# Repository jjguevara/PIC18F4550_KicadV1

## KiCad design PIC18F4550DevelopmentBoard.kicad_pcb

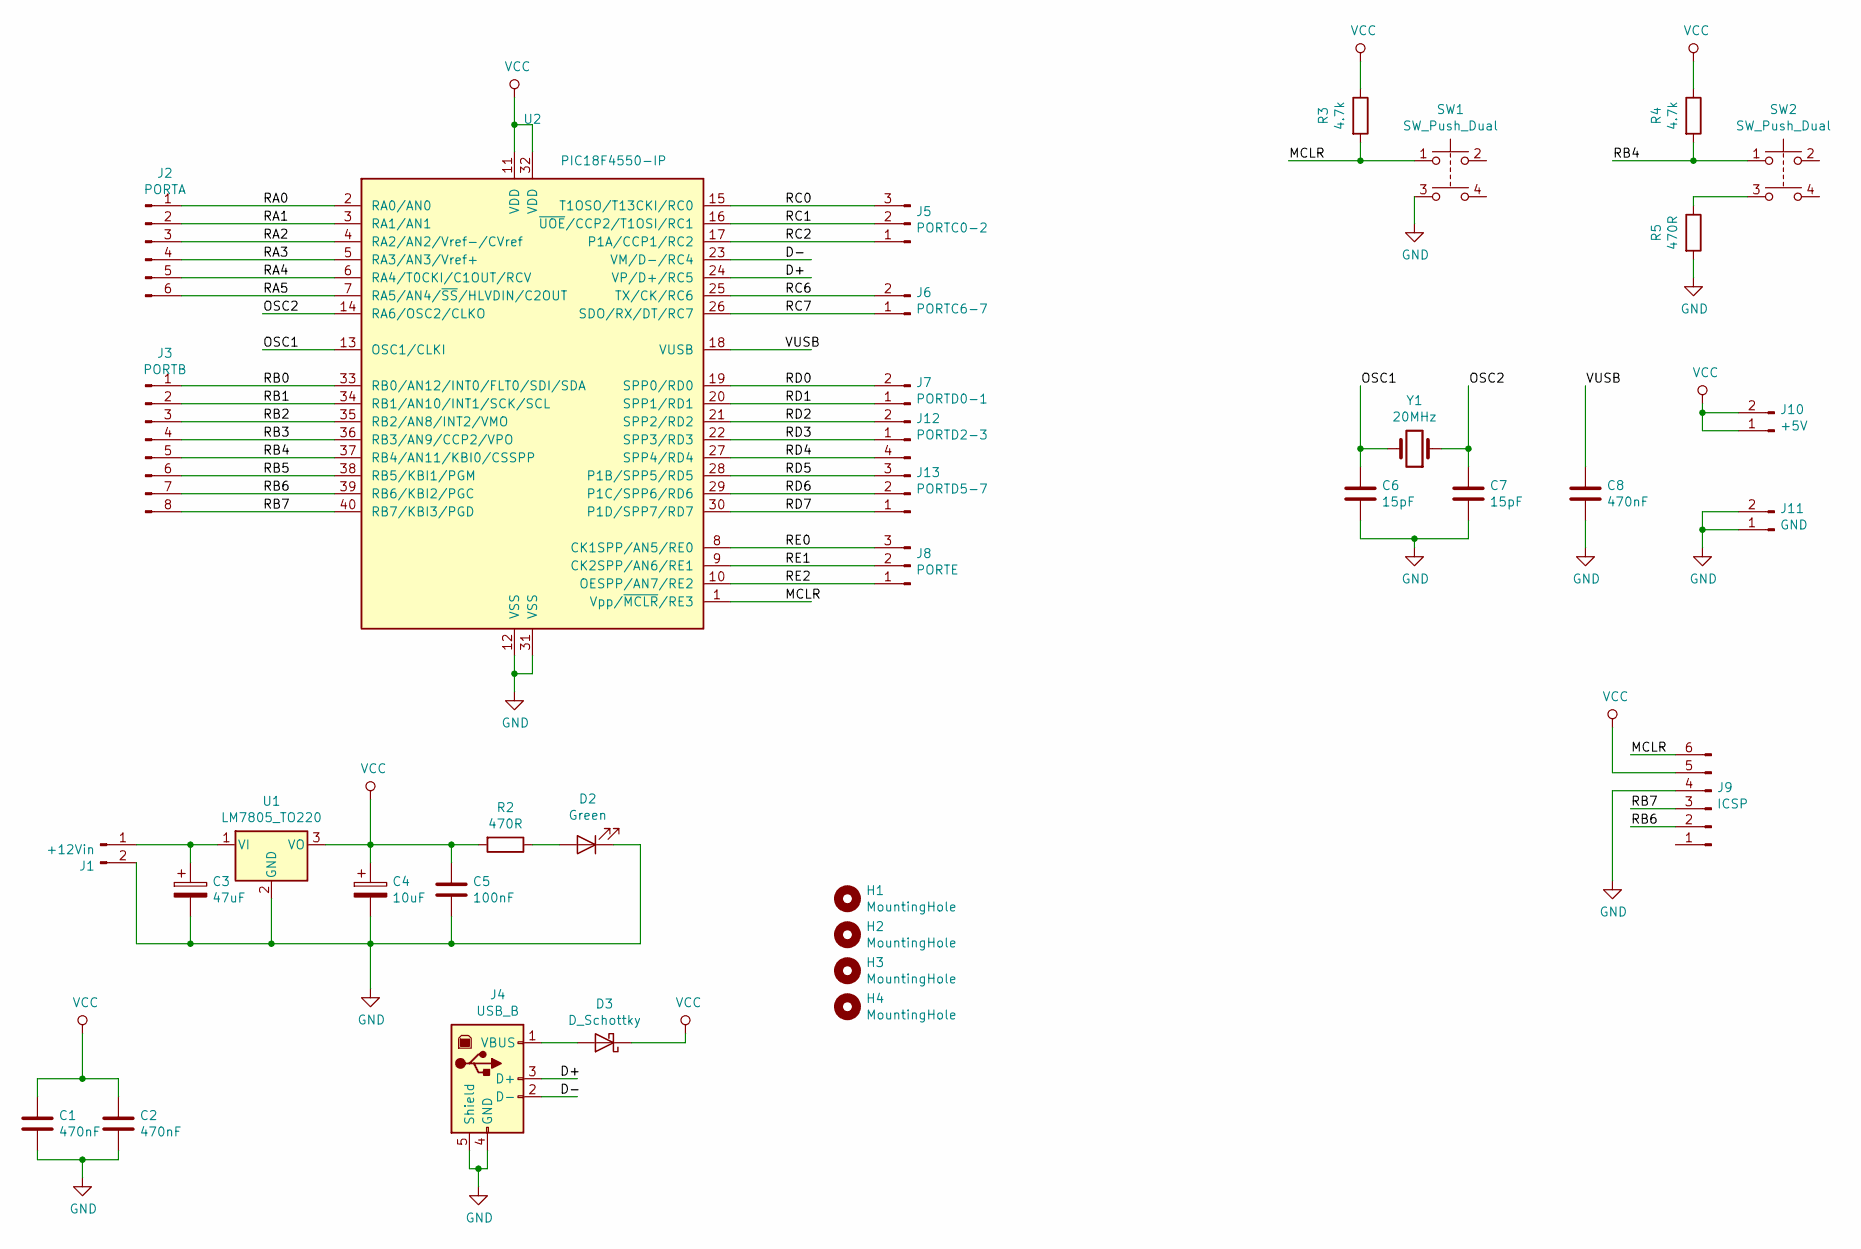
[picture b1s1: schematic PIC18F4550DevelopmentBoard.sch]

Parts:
C1, C2, C8: 470nF; C_Rect_L7.0mm_W2.5mm_P5.00mm
C3: 47uF; C_Radial_D5.0mm_H5.0mm_P2.00mm
C4: 10uF; C_Radial_D5.0mm_H5.0mm_P2.00mm
C5: 100nF; C_Rect_L7.0mm_W2.5mm_P5.00mm
C6, C7: 15pF; C_Disc_D3.0mm_W2.0mm_P2.50mm
D2: Green; LED_D3.0mm
D3: D_Schottky; D_DO-15_P15.24mm_Horizontal
H1, H2, H3, H4: MountingHole; MountingHole_3mm
J1: +12Vin; PinSocket_1x02_P2.54mm_Vertical
J2: PORTA; PinSocket_1x06_P2.54mm_Vertical
J3: PORTB; PinSocket_1x08_P2.54mm_Vertical
J4: USB_B; USB_B_OST_USB-B1HSxx_Horizontal
J5: PORTC0-2; PinSocket_1x03_P2.54mm_Vertical
J6: PORTC6-7; PinSocket_1x02_P2.54mm_Vertical
J7: PORTD0-1; PinSocket_1x02_P2.54mm_Vertical
J8: PORTE; PinSocket_1x03_P2.54mm_Vertical
J9: ICSP; PinSocket_1x06_P2.54mm_Vertical
J10: +5V; PinSocket_1x02_P2.54mm_Vertical
J11: GND; PinSocket_1x02_P2.54mm_Vertical
J12: PORTD2-3; PinSocket_1x02_P2.54mm_Vertical
J13: PORTD5-7; PinHeader_1x04_P2.54mm_Vertical
R2, R5: 470R; R_Axial_DIN0207_L6.3mm_D2.5mm_P10.16mm_Horizontal
R3, R4: 4.7k; R_Axial_DIN0207_L6.3mm_D2.5mm_P10.16mm_Horizontal
SW1, SW2: SW_Push_Dual; SW_TH_Tactile_Omron_B3F-10xx
U1: LM7805_TO220; TO-220-3_Vertical
U2: PIC18F4550-IP; DIP-40_W15.24mm
Y1: 20MHz; Crystal_HC49-U_Vertical

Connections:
/D+: J4.3 (D+), U2.24 (VP/D+/RC5)
/D-: J4.2 (D-), U2.23 (VM/D-/RC4)
/MCLR: J9.6, R3.2, SW1.1, U2.1 (Vpp/~MCLR~/RE3)
/OSC1: C6.1, U2.13 (OSC1/CLKI), Y1.2
/OSC2: C7.1, U2.14 (RA6/OSC2/CLKO), Y1.1
/RA0: J2.1, U2.2 (RA0/AN0)
/RA1: J2.2, U2.3 (RA1/AN1)
/RA2: J2.3, U2.4 (RA2/AN2/Vref-/CVref)
/RA3: J2.4, U2.5 (RA3/AN3/Vref+)
/RA4: J2.5, U2.6 (RA4/T0CKI/C1OUT/RCV)
/RA5: J2.6, U2.7 (RA5/AN4/~SS~/HLVDIN/C2OUT)
/RB0: J3.1, U2.33 (RB0/AN12/INT0/FLT0/SDI/SDA)
/RB1: J3.2, U2.34 (RB1/AN10/INT1/SCK/SCL)
/RB2: J3.3, U2.35 (RB2/AN8/INT2/VMO)
/RB3: J3.4, U2.36 (RB3/AN9/CCP2/VPO)
/RB4: J3.5, R4.2, SW2.1, U2.37 (RB4/AN11/KBI0/CSSPP)
/RB5: J3.6, U2.38 (RB5/KBI1/PGM)
/RB6: J3.7, J9.2, U2.39 (RB6/KBI2/PGC)
/RB7: J3.8, J9.3, U2.40 (RB7/KBI3/PGD)
/RC0: J5.3, U2.15 (T1OSO/T13CKI/RC0)
/RC1: J5.2, U2.16 (~UOE~/CCP2/T1OSI/RC1)
/RC2: J5.1, U2.17 (P1A/CCP1/RC2)
/RC6: J6.2, U2.25 (TX/CK/RC6)
/RC7: J6.1, U2.26 (SDO/RX/DT/RC7)
/RD0: J7.2, U2.19 (SPP0/RD0)
/RD1: J7.1, U2.20 (SPP1/RD1)
/RD2: J12.2, U2.21 (SPP2/RD2)
/RD3: J12.1, U2.22 (SPP3/RD3)
/RD4: J13.4, U2.27 (SPP4/RD4)
/RD5: J13.3, U2.28 (P1B/SPP5/RD5)
/RD6: J13.2, U2.29 (P1C/SPP6/RD6)
/RD7: J13.1, U2.30 (P1D/SPP7/RD7)
/RE0: J8.3, U2.8 (CK1SPP/AN5/RE0)
/RE1: J8.2, U2.9 (CK2SPP/AN6/RE1)
/RE2: J8.1, U2.10 (OESPP/AN7/RE2)
/VUSB: C8.1, U2.18 (VUSB)
GND: C1.2, C2.2, C3.2, C4.2, C5.2, C6.2, C7.2, C8.2, D2.1 (K), J1.2, J4.4 (GND), J4.5 (Shield), J9.4, J11.1, J11.2, R5.2, SW1.3, U1.2 (GND), U2.12 (VSS), U2.31 (VSS)
unnamed: C3.1, J1.1, U1.1 (VI)
unnamed: D2.2 (A), R2.1
unnamed: D3.2 (A), J4.1 (VBUS)
unnamed: R5.1, SW2.3
VCC: C1.1, C2.1, C4.1, C5.1, D3.1 (K), J9.5, J10.1, J10.2, R2.2, R3.1, R4.1, U1.3 (VO), U2.11 (VDD), U2.32 (VDD)

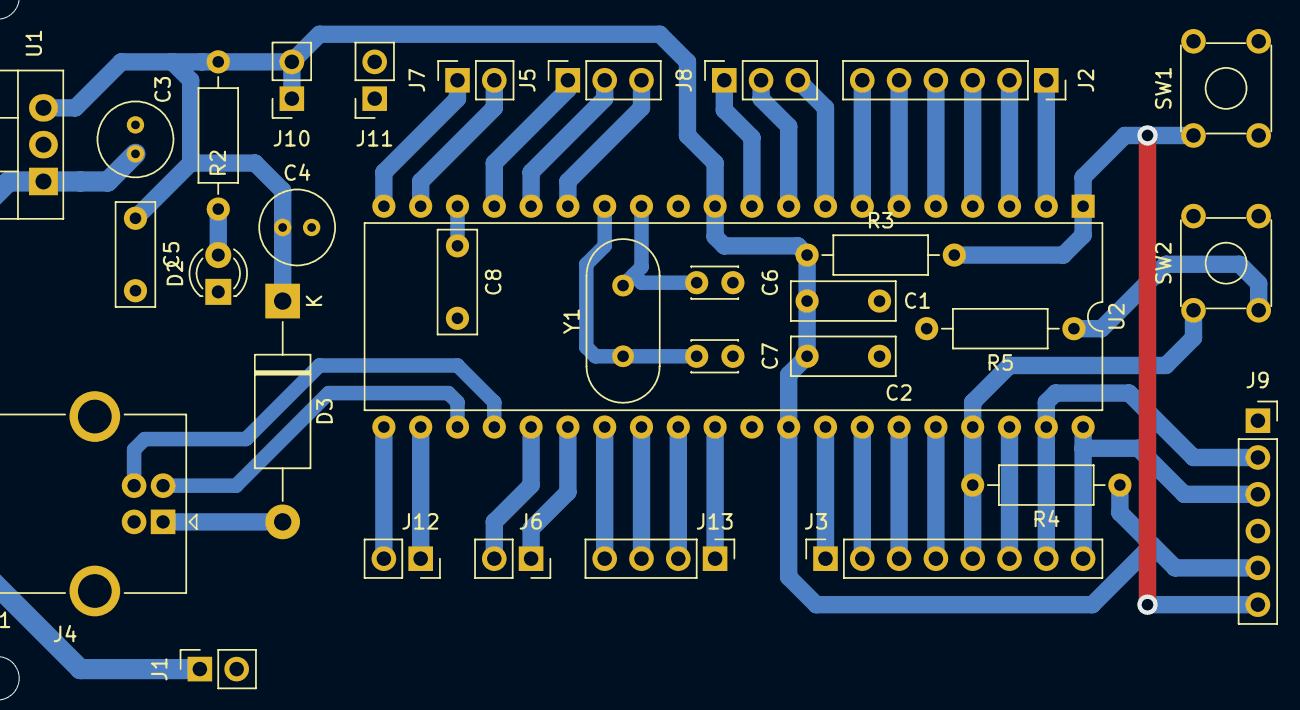
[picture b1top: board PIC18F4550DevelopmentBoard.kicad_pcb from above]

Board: 2 copper layers, 36 parts (0 on the bottom side), 42 nets.
